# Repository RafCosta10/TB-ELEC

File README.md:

# TB-ELEC

# Queen’s Hyperloop Electrical Subteam Repository

Welcome to the official repository for the Electrical Subteam of the Queen’s Hyperloop Tunnel & Boring group.

---

## 📋 About

This repository contains source code, firmware, design files, and documentation related to the electrical systems of our Hyperloop tunnel boring machine project. It is intended to support collaboration among current team members.

---

## 🚫 Usage Notice

This repository **does not have an open source license**.  
**All rights are reserved by the Queen’s Hyperloop Electrical Subteam.**  
The contents are provided for use *within the team only* and may not be copied, modified, or distributed outside the team without explicit permission.

---

## 📂 Repository Structure

- `/firmware` — Microcontroller code and scripts  
- `/tools` — Utilities and scripts supporting development  

---

## 🛠 Getting Started

- Please contact the Electrical Subteam Lead to request access or onboarding help.  
- Refer to the [Engineering Wiki](https://www.notion.so/235706a097758006bf46ff2deb52e041?v=235706a0977580078a06000c86afb2b6) for tutorials and guidelines.  
- Check the [Projects Dashboard](https://www.notion.so/235706a097758070890ec096f4407239?v=235706a097758027b426000c77134180) for current tasks and assignments.

---

## 🤝 Contribution

If you are a member of the Electrical Subteam and want to contribute:  
- Follow the team’s Git workflow guidelines (branching, commits, pull requests).  
- Coordinate with the project owner for reviews and testing.  

---

## 📞 Contact

Electrical Subteam Lead: [Rafael Costa] — [22xwyk@queensu.ca]  

---

Thanks for your interest and hard work! Let’s build something amazing together.

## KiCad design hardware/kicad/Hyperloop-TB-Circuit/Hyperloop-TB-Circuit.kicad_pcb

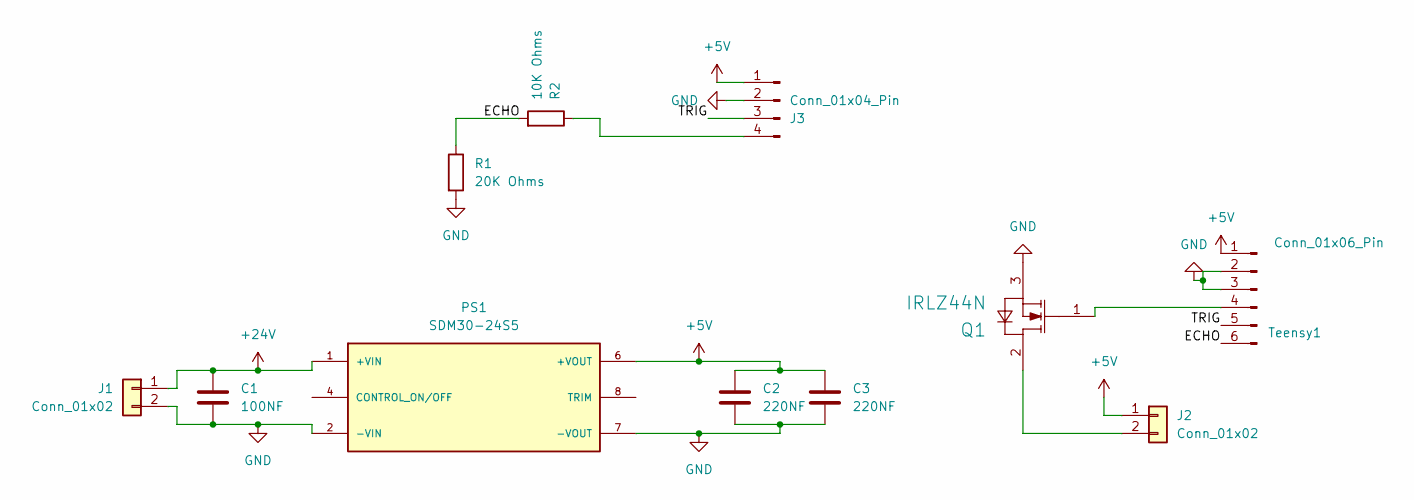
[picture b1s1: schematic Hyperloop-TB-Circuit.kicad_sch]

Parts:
C1: 100NF; C_Disc_D3.0mm_W1.6mm_P2.50mm
C2, C3: 220NF; C_Disc_D3.0mm_W1.6mm_P2.50mm
J1, J2: Conn_01x02; PinHeader_1x02_P1.00mm_Vertical
J3: Conn_01x04_Pin; Samtec_HPM-04-01-x-S_Straight_1x04_Pitch5.08mm
PS1: SDM30-24S5; CONV_SDM30-24S5; PARTREV 2018-01-12
Q1: IRLZ44N; IFX-PG-TO220-3-904-1
R1: 20K Ohms; R_Axial_DIN0204_L3.6mm_D1.6mm_P7.62mm_Horizontal
R2: 10K Ohms; R_Axial_DIN0204_L3.6mm_D1.6mm_P7.62mm_Horizontal
Teensy1: Conn_01x06_Pin; PinHeader_1x06_P1.00mm_Vertical

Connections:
+5V: C2.1, C3.1, J2.1, J3.1, PS1.6 (+VOUT), Teensy1.1
+24V: C1.1, J1.1, PS1.1 (+VIN)
/ECHO: R1.1, R2.2, Teensy1.6
/TRIG: J3.3, Teensy1.5
GND: C1.2, C2.2, C3.2, J1.2, J3.2, PS1.2 (-VIN), PS1.7 (-VOUT), Q1.3 (SOURCE), R1.2, Teensy1.2, Teensy1.3
unnamed: J2.2, Q1.2 (DRAIN)
unnamed: J3.4, R2.1
unnamed: Q1.1 (GATE), Teensy1.4

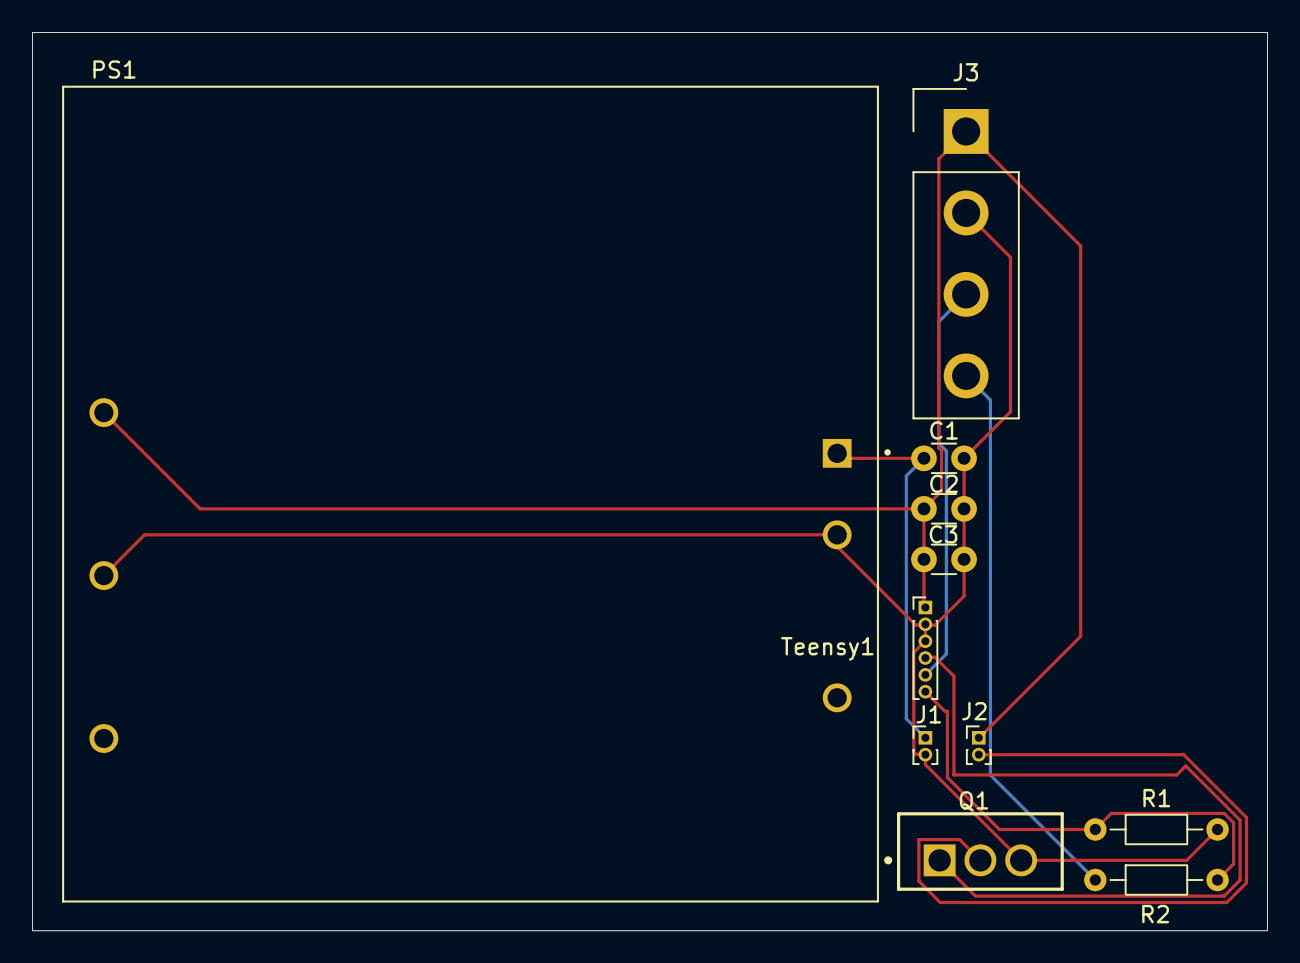
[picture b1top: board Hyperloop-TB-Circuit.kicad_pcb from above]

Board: 2 copper layers, 77.0 x 56.0 mm, 11 parts (0 on the bottom side), 8 nets.

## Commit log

2025-09-01 Competition information.
2026-02-01 Initialize main.c with state enumeration and function prototypes
2026-02-01 Add INVALID state and update function prototypes in main.c
2026-02-08 Fix variable declaration for current_state in main function and add VSCode settings for compiler path
2026-02-18 Added datasheets and parts
2026-02-18 Adding kicad files to the project
2026-02-19 Adding Kicad project libraries
2026-02-19 Kicad cicuit diagram
2026-02-20 Refactor code structure for improved readability and maintainability
2026-02-20 Finishing kicad drawing
2026-02-23 Update telemetry display title for clarity
2026-03-01 Adding footprint lib
2026-03-01 changing file location
2026-03-01 Halfway
2026-03-01 Pushing file for Jacob
2026-03-08 adding hardware files
2026-03-08 changed hardware
2026-03-08 saved
2026-03-08 Mosfet Symbol and Footprint
2026-03-08 Mosfet added to library
2026-03-08 Mosfet footprint to kicad library
2026-03-08 Connected Resistor Footprints to schematic
2026-03-08 changed lib
2026-03-08 Add GUI functionality and telemetry display for system monitoring
    - Introduced a new GUI module to visualize system states including voltage, current, temperature, and RPM.
    - Implemented buttons for controlling system states such as arm, disarm, start, and emergency stop.
    - Enhanced telemetry features to provide real-time updates on system parameters.
    - Added error handling for socket connections and JSON parsing.
    - Improved user interface responsiveness and aesthetics with custom styles.
2026-03-08 Connected all the parts to a footprint schematic
2026-03-08 HC-SR04 Ultrasonic Sonar Distance Sensor footprint (lit just 4 pins)
2026-03-08 Ultrasonic footprint (4pins for jumper wires)
2026-03-08 Schematic
2026-03-08 hello
2026-03-10 Reposition components in KiCad schematic
    Update Hyperloop-TB-Circuit.kicad_sch with numerous coordinate adjustments (junctions, wires, labels and symbol positions) to tidy up the schematic layout. Also update the Teensy 4.1 example schemati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
2026-03-15 adding motor
2026-03-15 connected footprints
2026-03-15 updated schematic and pcb
2026-03-19 new pcb
2026-03-26 Add new ultra_motor_test.ino file
2026-03-26 ardunio code
2026-03-26 Add ultra_motor_test.ino for motor and ultrasonic sensor control
